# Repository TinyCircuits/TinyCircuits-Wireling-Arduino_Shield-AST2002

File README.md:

# TinyCircuits Wireling Arduino Shield AST2002
# AST2002 Rev2

The design files are located under design_files/ for the TinyCircuits AST2002 Rev 2 PCB. This is a Standard Arduino Shield that allows Standard Arduino users to connect up to 4 Wirelings to their Arduino projects.

Format is in Cadsoft Eagle format - Eagle version 6.2 was used for the original design.

For more infomation on this, check out the product page at TinyCircuits.com

# License:

Design by TinyCircuits.
All design files are released under the Creative Commons Attribution Share-Alike 3.0 License, see the following link for details: http://creativecommons.org/licenses/by-sa/3.0

All text above must be included in any redistribution or derived design

This project uses designs and concepts developed as part of the Arduino project and the LilyPad project.  The TinyCircuits design files themselves (schematics, PCB and libraries) are not directly derived from these works' design files and have been created new, however the concepts and basic architecture behind the TinyDuino and TinyLily products are derived and we thank the hard work of the organizations below for their contributions to open-source hardware:
  
Original Arduino Uno Design by Team Arduino

LilyPad Arduino Design by Leah Buechley and Sparkfun Electronics

Please support the open-source hardware community

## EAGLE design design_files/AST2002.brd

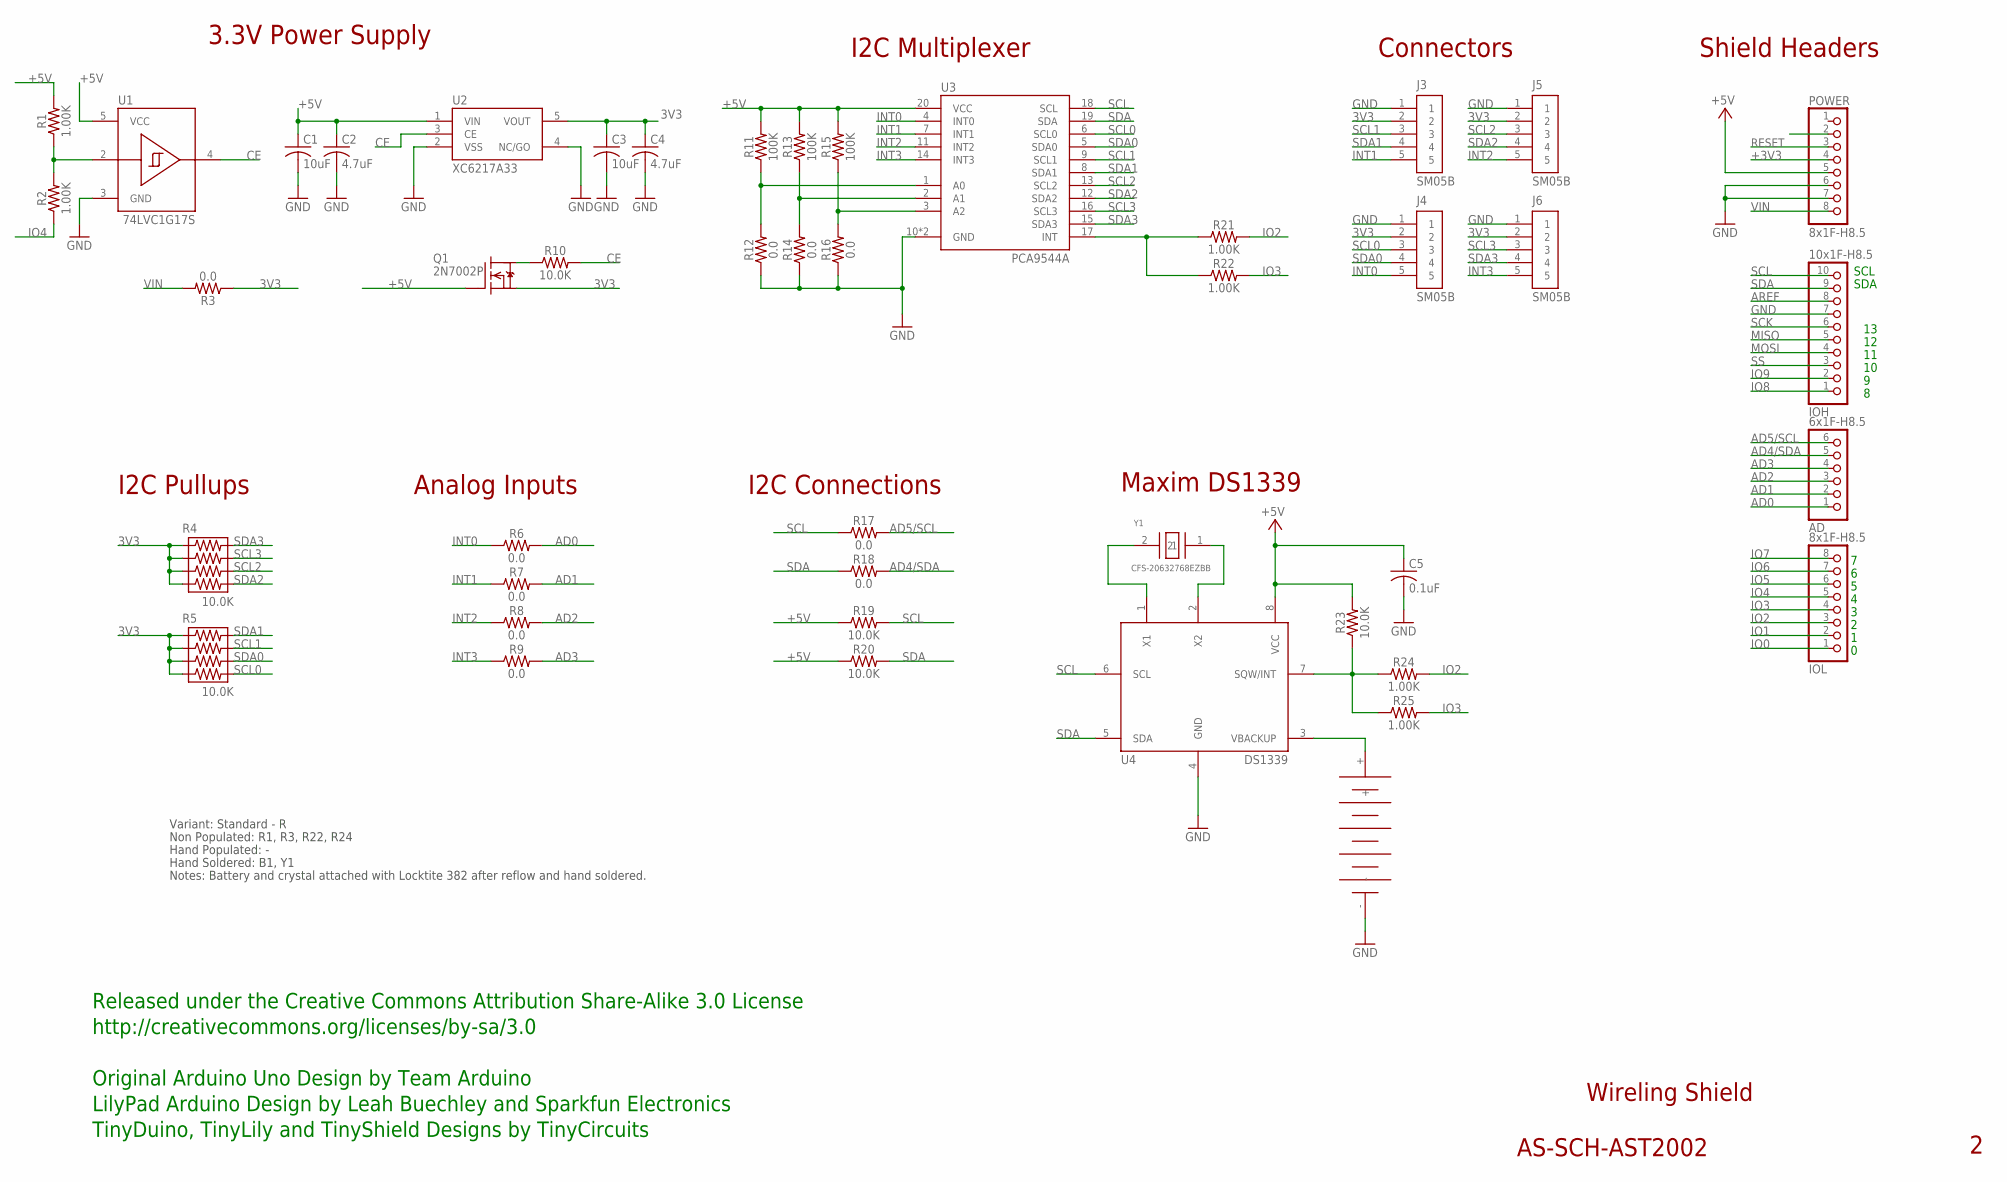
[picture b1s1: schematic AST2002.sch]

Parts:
AD: 6x1F-H8.5; 1X06
B1: ML-920S/DN
C1: 10uF; C0603; PARTNO AS-ITM-00002
C2, C4: 4.7uF; C0402; PARTNO AS-ITM-00242
C3: 10uF; C0603
C5: 0.1uF; C0402
IOH: 10x1F-H8.5; 1X10
IOL: 8x1F-H8.5; 1X08
J3, J4, J5, J6: SM05B; JST_SH_5X1
POWER: 8x1F-H8.5; 1X08
Q1: 2N7002P; SOT-416; PARTNO AS-ITM-00110
R1, R2, R24, R25: 1.00K; 0402; PARTNO AS-ITM-00003
R3, R12, R14, R16: 0.0; 0402; PARTNO AS-ITM-00076
R4, R5: 10.0K; 0402RPACK; PARTNO AS-ITM-00520
R6, R7, R8, R9, R17, R18: 0.0; 0402
R10, R23: 10.0K; 0402; PARTNO AS-ITM-00032
R11, R13, R15: 100K; 0402; PARTNO AS-ITM-00004
R19, R20: 10.0K; 0402
R21, R22: 1.00K; 0402
U1: 74LVC1G17S; SOT-353
U2: XC6217A33; SOT-25; PARTNO AS-ITM-00249
U3: PCA9544A; VQFN-20_4.5X3.5
U4: DS1339; 8-USOP
Y1: CFS-20632768EZBB; CRYSTAL_1.9MM_TH

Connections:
3V3: C3.1, C4.1, J3.2, J4.2, J5.2, J6.2, Q1.2 (S), R3.1, R4.1, R4.3, R4.5, R4.7, R5.1, R5.3, R5.5, R5.7, U2.5 (VOUT)
+3V3: POWER.4
+5V: C1.1, C2.1, C5.1, POWER.5, Q1.1 (G), R1.2, R11.2, R13.2, R15.2, R19.1, R20.1, R23.2, U1.5 (VCC), U2.1 (VIN), U3.20 (VCC), U4.8 (VCC)
AD0: AD.1, R6.2
AD1: AD.2, R7.2
AD2: AD.3, R8.2
AD3: AD.4, R9.2
AD4/SDA: AD.5, R18.2
AD5/SCL: AD.6, R17.2
AREF: IOH.8
CE: R10.2, U1.4 (Y), U2.3 (CE)
GND: B1.-, C1.2, C2.2, C3.2, C4.2, C5.2, IOH.7, J3.1, J4.1, J5.1, J6.1, POWER.6, POWER.7, R12.1, R14.1, R16.1, U1.3 (GND), U2.2 (VSS), U2.4 (NC/GO), U3.10 (GND), U3.PAD (GND), U4.4 (GND)
INT0: J4.5, R6.1, U3.4 (INT0)
INT1: J3.5, R7.1, U3.7 (INT1)
INT2: J5.5, R8.1, U3.11 (INT2)
INT3: J6.5, R9.1, U3.14 (INT3)
IO0: IOL.1
IO1: IOL.2
IO2: IOL.3, R21.2, R24.2
IO3: IOL.4, R22.2, R25.2
IO4: IOL.5, R2.1
IO5: IOL.6
IO6: IOL.7
IO7: IOL.8
IO8: IOH.1
IO9: IOH.2
MISO: IOH.5
MOSI: IOH.4
unnamed: Q1.3 (D), R10.1
unnamed: R11.1, R12.2, U3.1 (A0)
unnamed: R15.1, R16.2, U3.3 (A2)
unnamed: R21.1, R22.1, U3.17 (INT)
unnamed: R13.1, R14.2, U3.2 (A1)
unnamed: R23.1, R24.1, R25.1, U4.7 (SQW/INT)
unnamed: B1.+, U4.3 (VBACKUP)
unnamed: U4.1 (X1), Y1.2 (1)
unnamed: U4.2 (X2), Y1.1 (2)
unnamed: R1.1, R2.2, U1.2 (A)
RESET: POWER.3
SCK: IOH.6
SCL: IOH.10, R17.1, R19.2, U3.18 (SCL), U4.6 (SCL)
SCL0: J4.3, R5.8, U3.6 (SCL0)
SCL1: J3.3, R5.4, U3.9 (SCL1)
SCL2: J5.3, R4.6, U3.13 (SCL2)
SCL3: J6.3, R4.4, U3.16 (SCL3)
SDA: IOH.9, R18.1, R20.2, U3.19 (SDA), U4.5 (SDA)
SDA0: J4.4, R5.6, U3.5 (SDA0)
SDA1: J3.4, R5.2, U3.8 (SDA1)
SDA2: J5.4, R4.8, U3.12 (SDA2)
SDA3: J6.4, R4.2, U3.15 (SDA3)
SS: IOH.3
VIN: POWER.8, R3.2

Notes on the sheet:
Shield Headers
Wireling Shield
AS-SCH-AST2002
Released under the Creative Commons Attribution Share-Alike 3.0 License
http://creativecommons.org/licenses/by-sa/3.0
LilyPad Arduino Design by Leah Buechley and Sparkfun Electronics
TinyDuino, TinyLily and TinyShield Designs by TinyCircuits
Original Arduino Uno Design by Team Arduino
3.3V Power Supply
I2C Multiplexer
Connectors
Analog Inputs
I2C Pullups
Non Populated: R1, R3, R22, R24
Variant: Standard - R
SDA
SCL
Maxim DS1339
Hand Populated: -
Hand Soldered: B1, Y1
Notes: Battery and crystal attached with Locktite 382 after reflow and hand soldered.
I2C Connections

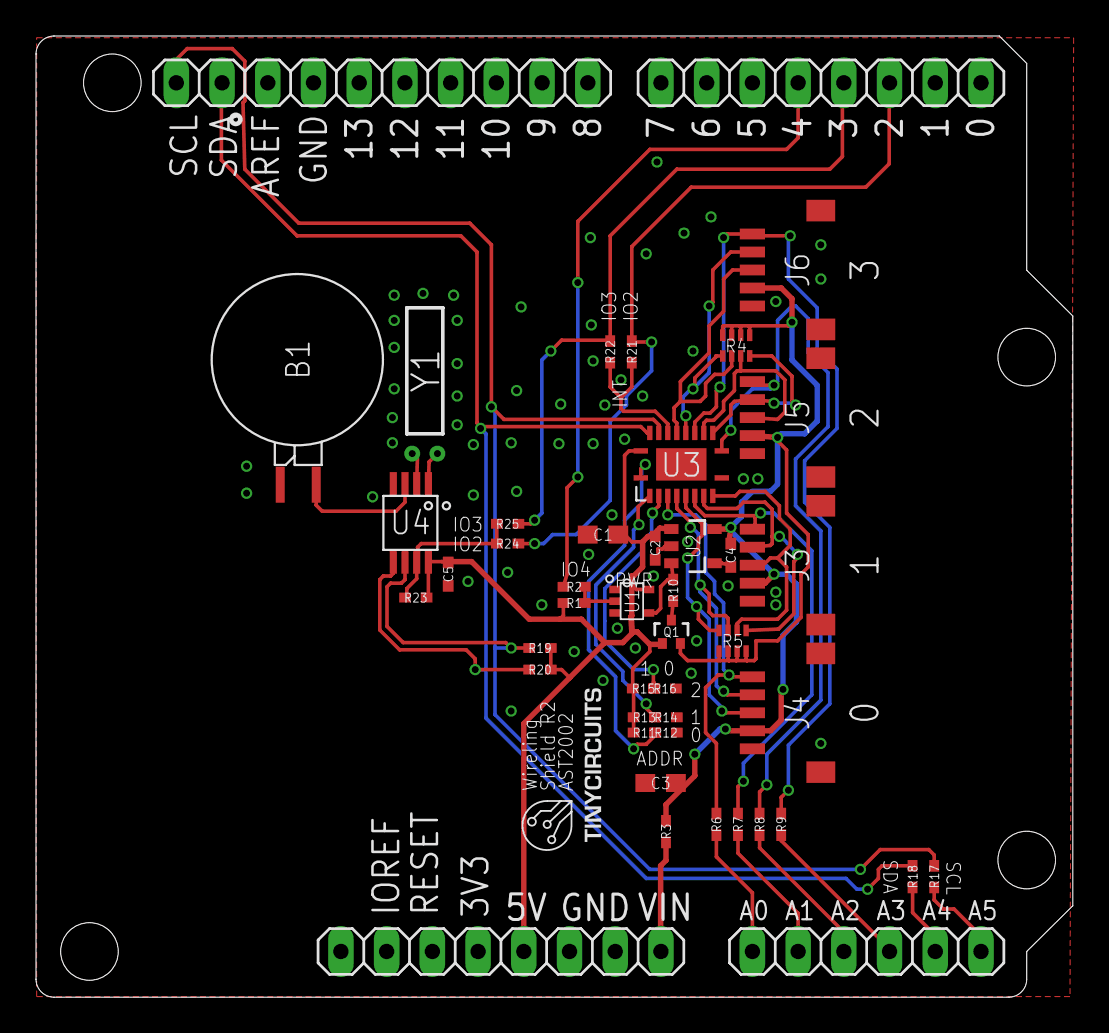
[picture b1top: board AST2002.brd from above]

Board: 2 copper layers, 57.6 x 53.4 mm, 46 parts (0 on the bottom side), 38 nets.

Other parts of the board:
U$1: DOCFIELD-TINYCIRCUITS-PCB

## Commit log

2019-12-10 first init
2019-12-10 docs
2020-08-14 Add CAD data
